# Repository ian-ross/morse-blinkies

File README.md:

# Morse code blinkies with KiCad, Espresso and SKIDL!

Silly project, explained
[here](https://www.skybluetrades.net/projects/morse-blinkies-as-a-service/).

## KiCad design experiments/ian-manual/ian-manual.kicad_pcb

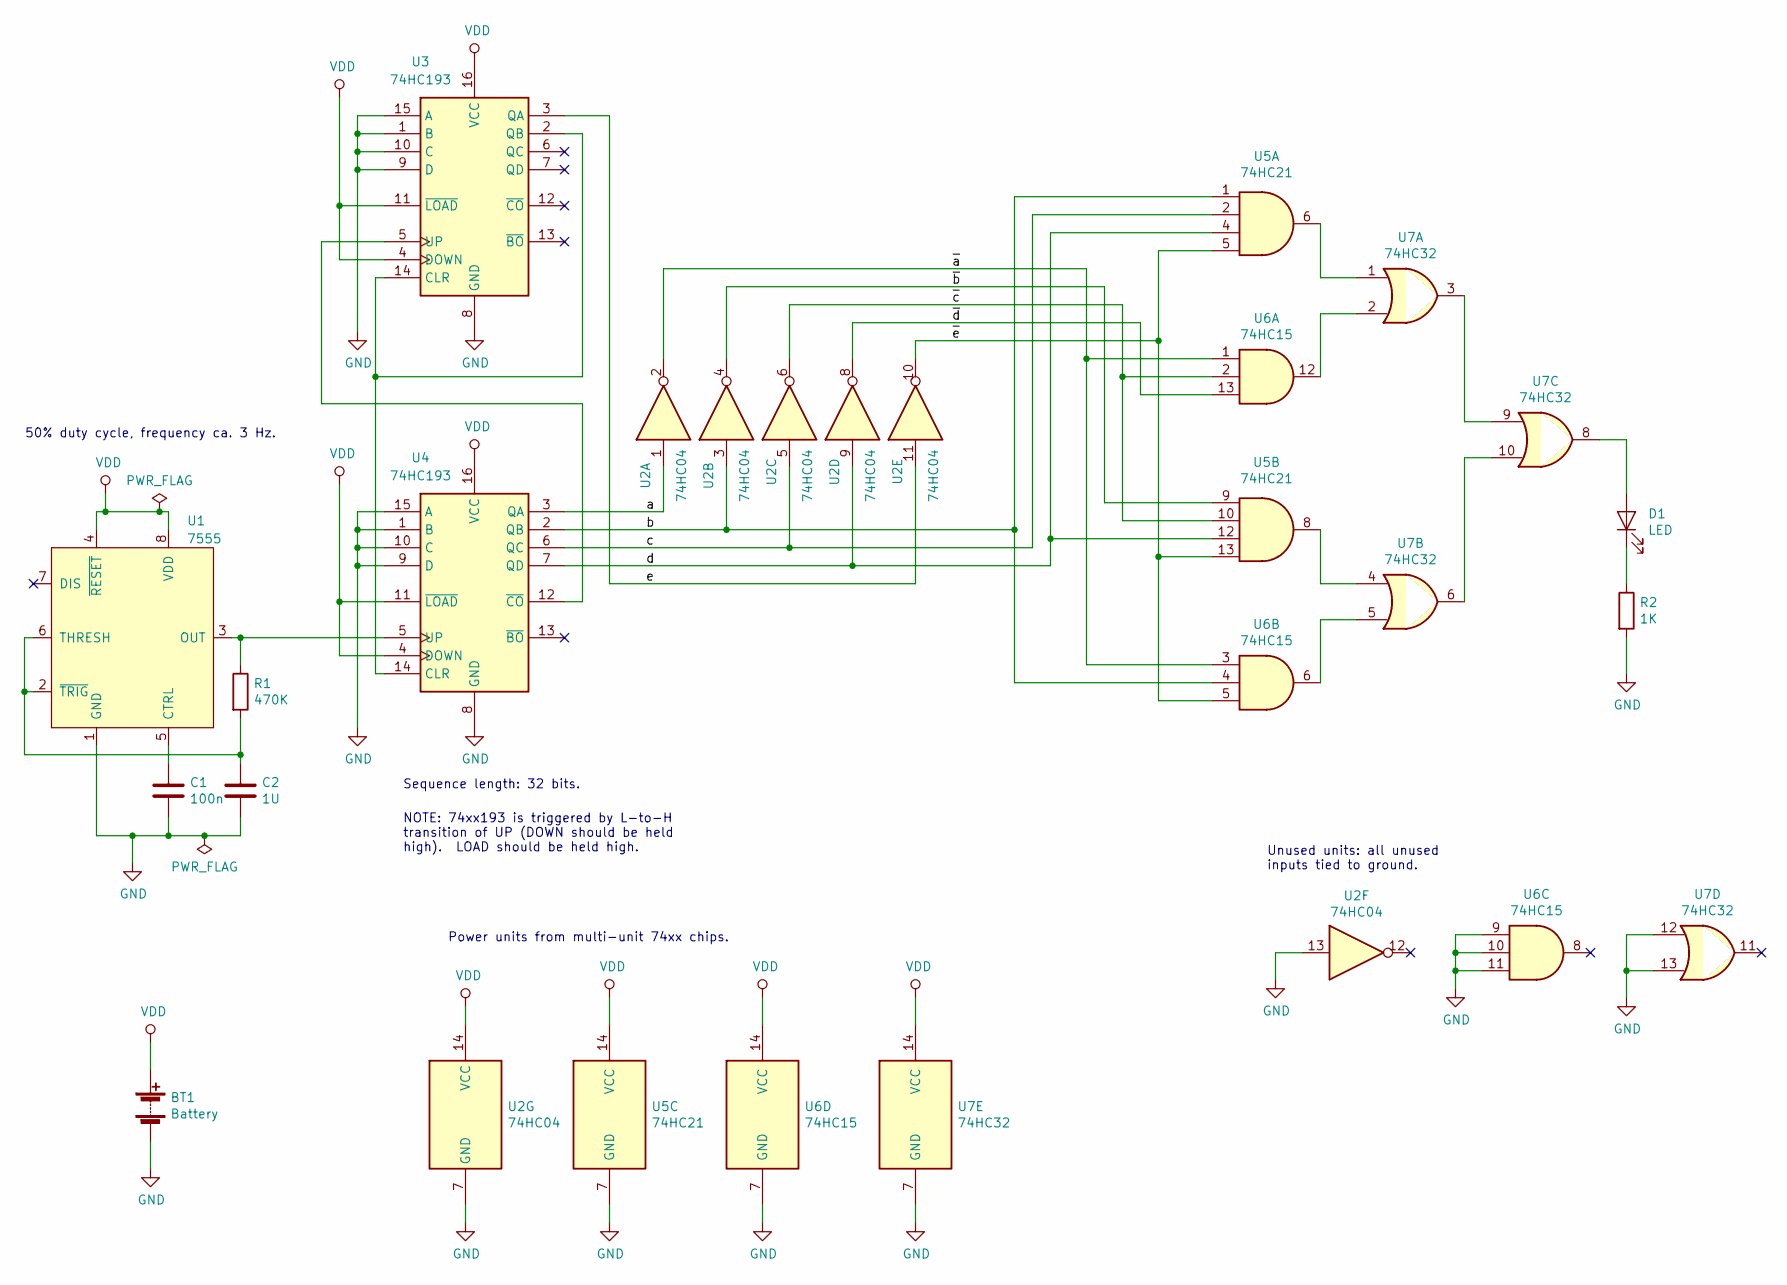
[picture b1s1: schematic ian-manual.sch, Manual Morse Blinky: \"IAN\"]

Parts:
BT1: Battery; BatteryHolder_LINK_BAT-HLD-001-SMT
C1: 100n; C_0805_2012Metric_Pad1.15x1.40mm_HandSolder
C2: 1U; C_0805_2012Metric_Pad1.15x1.40mm_HandSolder
D1: LED; LED_0805_2012Metric_Pad1.15x1.40mm_HandSolder
R1: 470K; R_0805_2012Metric_Pad1.15x1.40mm_HandSolder
R2: 1K; R_0805_2012Metric_Pad1.15x1.40mm_HandSolder
U1: 7555; SOIC-8_3.9x4.9mm_P1.27mm
U2: 74HC04; SOIC-14_3.9x8.7mm_P1.27mm
U3, U4: 74HC193; SOIC-16_3.9x9.9mm_P1.27mm
U5: 74HC21; SOIC-14_3.9x8.7mm_P1.27mm
U6: 74HC15; SOIC-14_3.9x8.7mm_P1.27mm
U7: 74HC32; SOIC-14_3.9x8.7mm_P1.27mm

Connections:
/a: U2.1, U4.3 (QA)
/b: U2.3, U4.2 (QB), U5.1, U6.4
/c: U2.5, U4.6 (QC), U5.2
/d: U2.9, U4.7 (QD), U5.4, U5.12
/e: U2.11, U3.3 (QA)
/~a: U2.2, U6.1, U6.3
/~b: U2.4, U5.9
/~c: U2.6, U5.10, U6.2
/~d: U2.8, U6.13
/~e: U2.10, U5.5, U5.13, U6.5
GND: BT1.2 (-), C1.2, C2.2, R2.2, U1.1 (GND), U2.7 (GND), U2.13, U3.1 (B), U3.8 (GND), U3.9 (D), U3.10 (C), U3.15 (A), U4.1 (B), U4.8 (GND), U4.9 (D), U4.10 (C), U4.15 (A), U5.7 (GND), U6.7 (GND), U6.9, U6.10, U6.11, U7.7 (GND), U7.12, U7.13
unnamed: C1.1, U1.5 (CTRL)
unnamed: C2.1, R1.2, U1.2 (~TRIG), U1.6 (THRESH)
unnamed: D1.1 (K), R2.1
unnamed: D1.2 (A), U7.8
unnamed: R1.1, U1.3 (OUT), U4.5 (UP)
unnamed: U3.5 (UP), U4.12 (~CO)
unnamed: U3.2 (QB), U3.14 (CLR), U4.14 (CLR)
unnamed: U5.6, U7.1
unnamed: U5.8, U7.4
unnamed: U6.6, U7.5
unnamed: U6.12, U7.2
unnamed: U7.3, U7.9
unnamed: U7.6, U7.10
VDD: BT1.1 (+), U1.4 (~RESET), U1.8 (VDD), U2.14 (VCC), U3.4 (DOWN), U3.11 (~LOAD), U3.16 (VCC), U4.4 (DOWN), U4.11 (~LOAD), U4.16 (VCC), U5.14 (VCC), U6.14 (VCC), U7.14 (VCC)

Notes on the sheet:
Unused units: all unused inputs tied to ground.
Power units from multi-unit 74xx chips.
50% duty cycle, frequency ca. 3 Hz.
Sequence length: 32 bits.
NOTE: 74xx193 is triggered by L-to-H transition of UP (DOWN should be held high). LOAD should be held high.

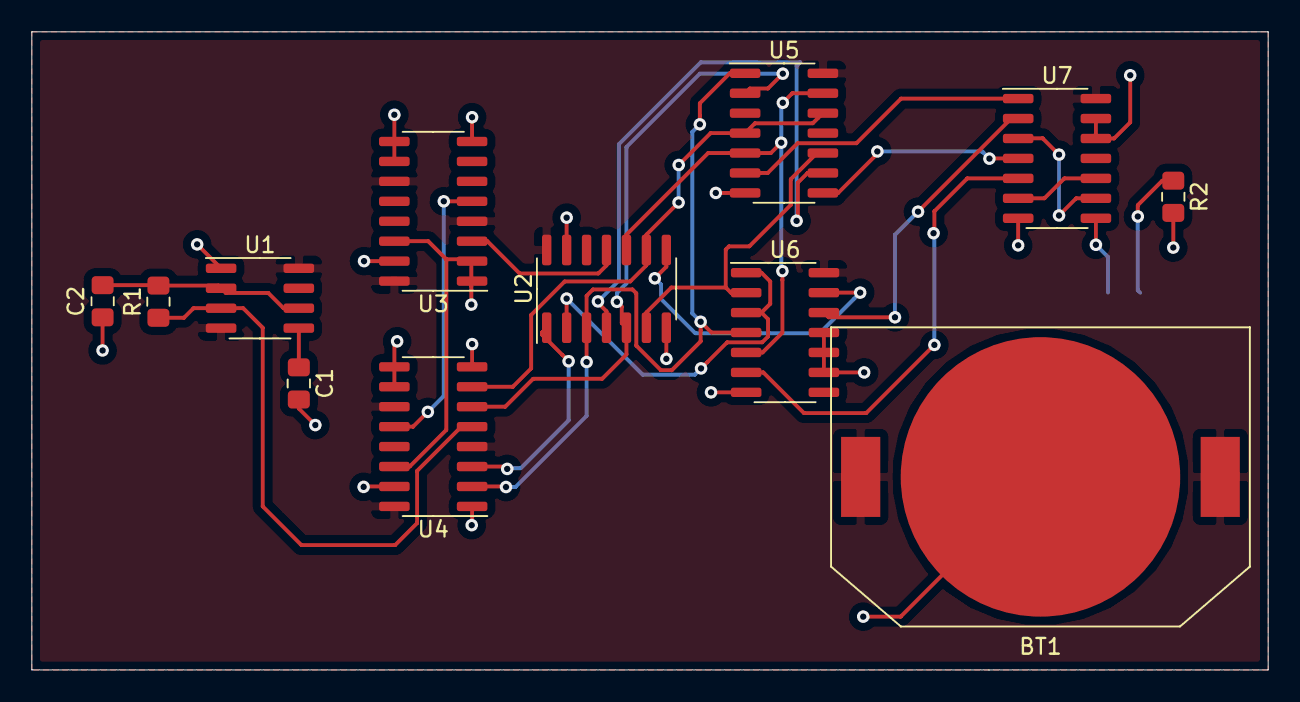
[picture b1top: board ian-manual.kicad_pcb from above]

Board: 2 copper layers, 78.7 x 40.6 mm, 13 parts (1 on the bottom side), 25 nets.

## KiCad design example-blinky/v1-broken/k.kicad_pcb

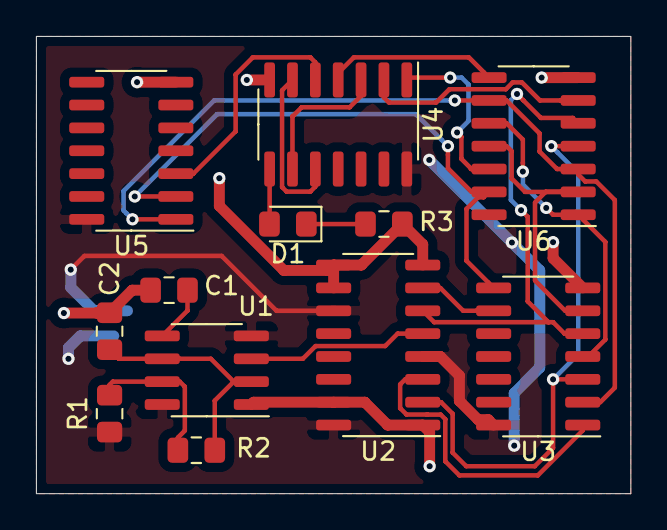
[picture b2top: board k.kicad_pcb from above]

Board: 2 copper layers, 33.0 x 25.4 mm, 13 parts (1 on the bottom side), 22 nets.

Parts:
BT1: 9V; BatteryHolder_LINK_BAT-HLD-001-SMT
C1: 100n; C_0805_2012Metric_Pad1.15x1.40mm_HandSolder
C2: 1U; C_0805_2012Metric_Pad1.15x1.40mm_HandSolder
D1: LED; LED_0805_2012Metric_Pad1.15x1.40mm_HandSolder
R1, R2: 56K; R_0805_2012Metric_Pad1.15x1.40mm_HandSolder
R3: 56; R_0805_2012Metric_Pad1.15x1.40mm_HandSolder
U1: 7555; SOIC-8_3.9x4.9mm_P1.27mm
U2: 74HC193; SOIC-16_3.9x9.9mm_P1.27mm
U3: 74HC04; SOIC-14_3.9x8.7mm_P1.27mm
U4: 74HC32; SOIC-14_3.9x8.7mm_P1.27mm
U5: 74HC08; SOIC-14_3.9x8.7mm_P1.27mm
U6: 74HC11; SOIC-14_3.9x8.7mm_P1.27mm

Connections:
GND: BT1.2, C1.2, C2.1, R3.2, U1.1, U2.1, U2.8, U2.9, U2.10, U2.15, U3.7, U4.7, U5.7, U6.7
unnamed: C1.1, U1.5
unnamed: C2.2, R2.1, U1.2, U1.6
unnamed: R1.1, R2.2, U1.7
unnamed: U1.3, U2.5
unnamed: U2.3, U3.1
unnamed: U3.2, U5.1, U6.3, U6.9
unnamed: U2.2, U3.3, U6.4
unnamed: U3.4, U6.1, U6.10
unnamed: U2.6, U3.5, U6.5
unnamed: U3.6, U6.2, U6.11
unnamed: U2.7, U3.9
unnamed: U3.8, U5.2, U6.13
unnamed: U4.5, U5.3
unnamed: U4.1, U6.12
unnamed: U4.2, U6.6
unnamed: U4.3, U4.9
unnamed: U4.4, U6.8
unnamed: U4.6, U4.10
unnamed: D1.2, U4.8
unnamed: D1.1, R3.1
VDD: BT1.1, R1.2, U1.4, U1.8, U2.4, U2.11, U2.16, U3.14, U4.14, U5.14, U6.14

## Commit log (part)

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2020-02-04 Initial experiments
2020-02-05 Starting on Go code
2020-02-05 Espresso processing
2020-02-15 Tidying; templates for web app
2020-02-15 Tidying
2020-02-17 WIP: sort of working...
2020-02-18 MOSFET drivers...
2020-02-21 Speed control
2020-02-21 BJT drivers
2020-02-21 Rules input
2020-02-23 Job queuing
2020-02-23 BOM generation
2020-02-23 Deployment cleanups
2020-02-24 Example blinky
2020-02-24 README
2020-03-15 Footprint fixes and example blinky respin
2022-06-22 Bump numpy from 1.18.1 to 1.22.0 in /mbaas/python
    Bumps [numpy](https://github.com/numpy/numpy) from 1.18.1 to 1.22.0.
    - [Release notes](https://github.com/numpy/numpy/releases)
    - [Changelog](https://github.com/numpy/numpy/blob/main/doc/HOWTO_RELEASE.rst)
    - [Commits](https://github.com/numpy/numpy/compare/v1.18.1...v1.22.0)
    ---
    updated-dependencies:
2025-08-22 Bump future from 0.18.2 to 1.0.0 in /mbaas/python
    Bumps [future](https://github.com/PythonCharmers/python-future) from 0.18.2 to 1.0.0.
    - [Release notes](https://github.com/PythonCharmers/python-future/releases)
    - [Changelog](https://github.com/PythonCharmers/python-future/blob/master/docs/changelog.rst)
    - [Commits](https://github.com/PythonCharmers/python-future/compare/v0.18.2...v1.0.0)
    ---
    updated-dependencies:
